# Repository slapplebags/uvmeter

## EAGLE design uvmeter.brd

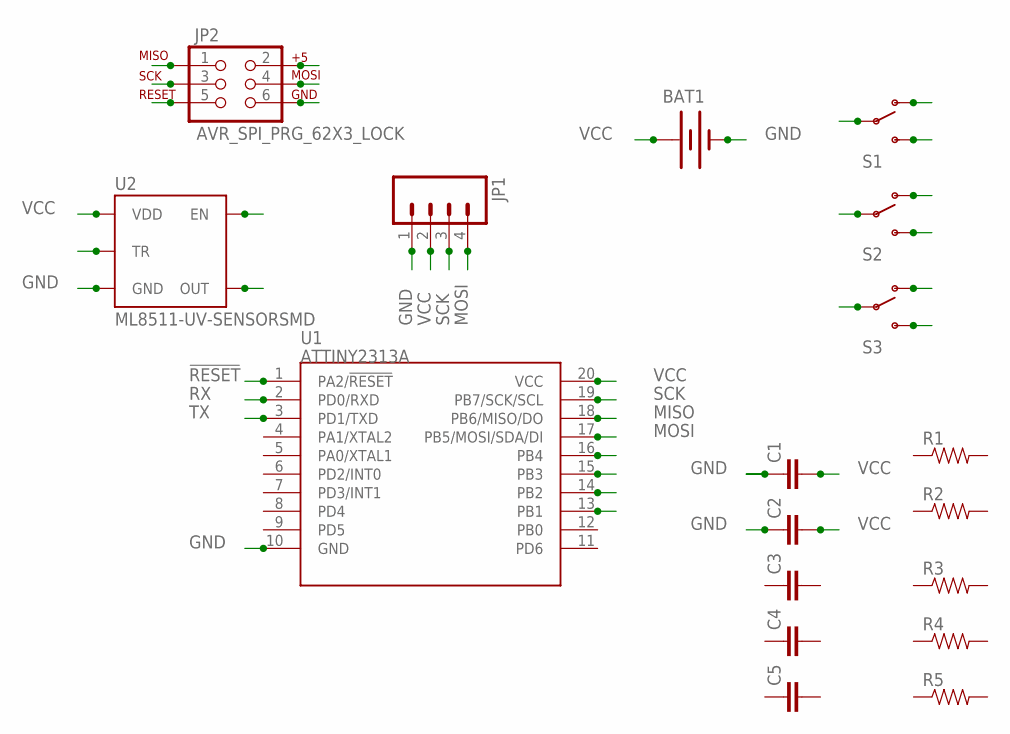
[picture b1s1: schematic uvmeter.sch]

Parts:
BAT1: BATTERY20SMD; BATTCON_20MM
C1, C2, C3, C4, C5: CAP0805; 0805
JP1: M04LONGPADS; 1X04_LONGPADS
JP2: AVR_SPI_PRG_62X3_LOCK; 2X3_LOCK
R1, R2, R3, R4, R5: RESISTOR0805-RES; 0805
S1, S2, S3: SWITCH-SPDTSMD2; SWITCH-SPDT-SMD
U1: ATTINY2313A; SOP20W
U2: ML8511-UV-SENSORSMD; ML8511

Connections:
!RESET: JP2.5, R2.1, U1.1 (PA2/!RESET)
D10: U1.13 (PB1)
D11: U1.14 (PB2)
D12: U1.15 (PB3)
D13: U1.16 (PB4)
EN: R1.1
GND: BAT1.2 (-), C1.1, C2.1, C3.1, JP1.1, JP2.6, U1.10 (GND), U2.5 (GND)
MISO: JP2.1, U1.18 (PB6/MISO/DO)
MOSI: JP1.4, JP2.4, R4.1, U1.17 (PB5/MOSI/SDA/DI)
RX: U1.2 (PD0/RXD)
SCK: JP1.3, JP2.3, R3.1, U1.19 (PB7/SCK/SCL)
TR: C3.2, U2.10 (TR)
TX: U1.3 (PD1/TXD)
VCC: BAT1.1 (+), C1.2, C2.2, JP1.2, JP2.2, R1.2, R2.2, R3.2, R4.2, U1.20 (VCC), U2.7 (VDD)

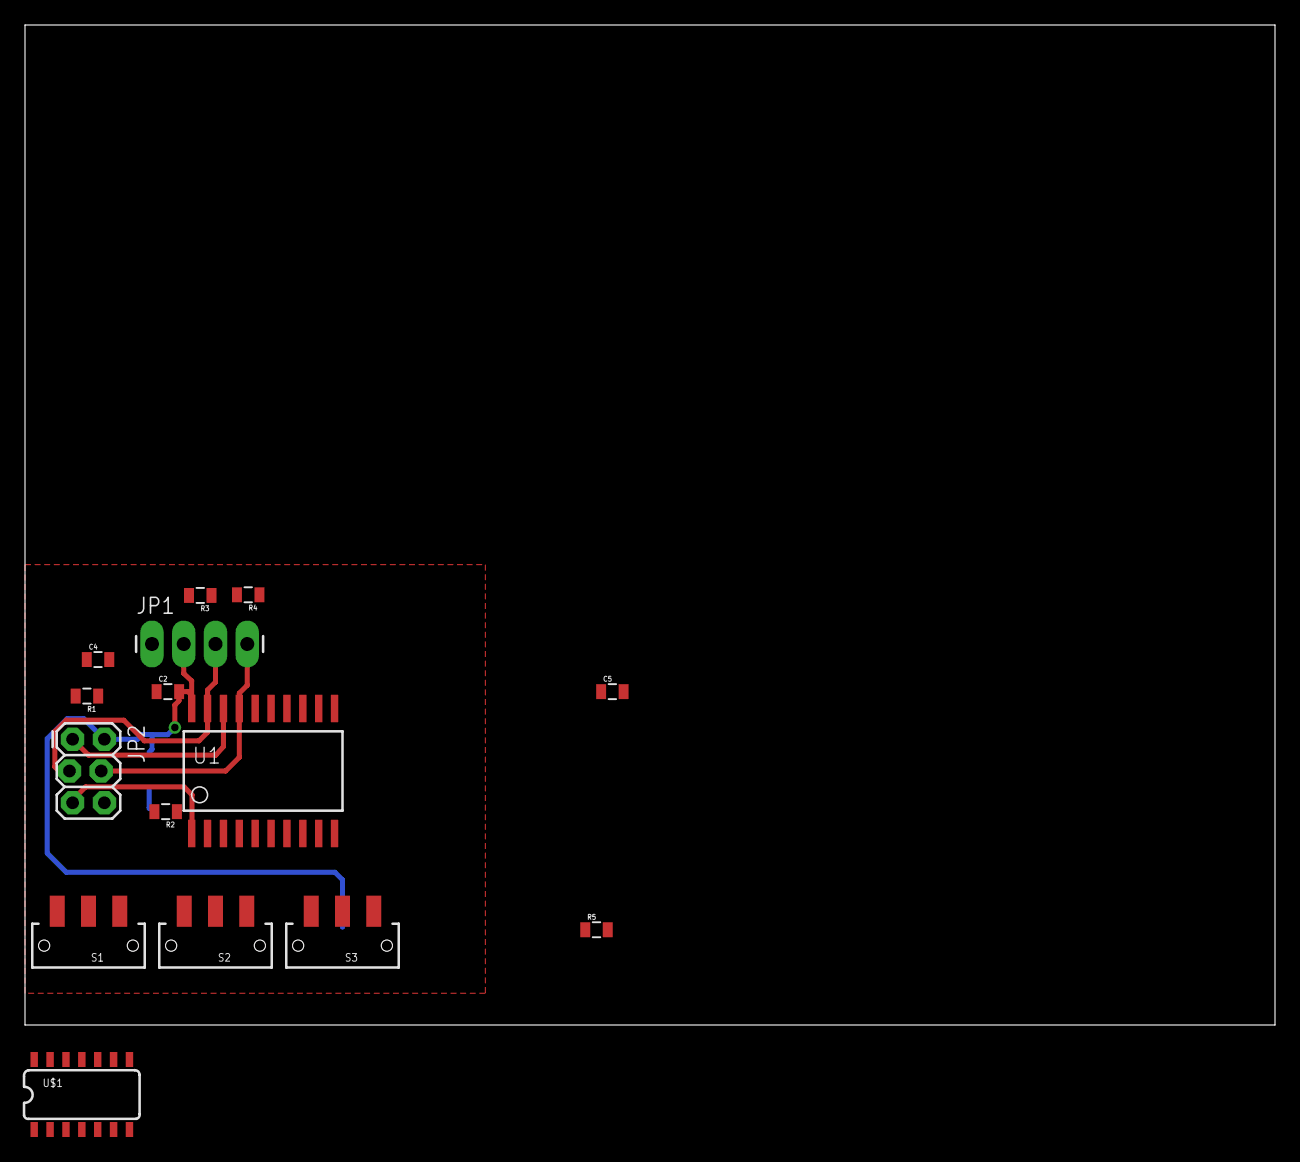
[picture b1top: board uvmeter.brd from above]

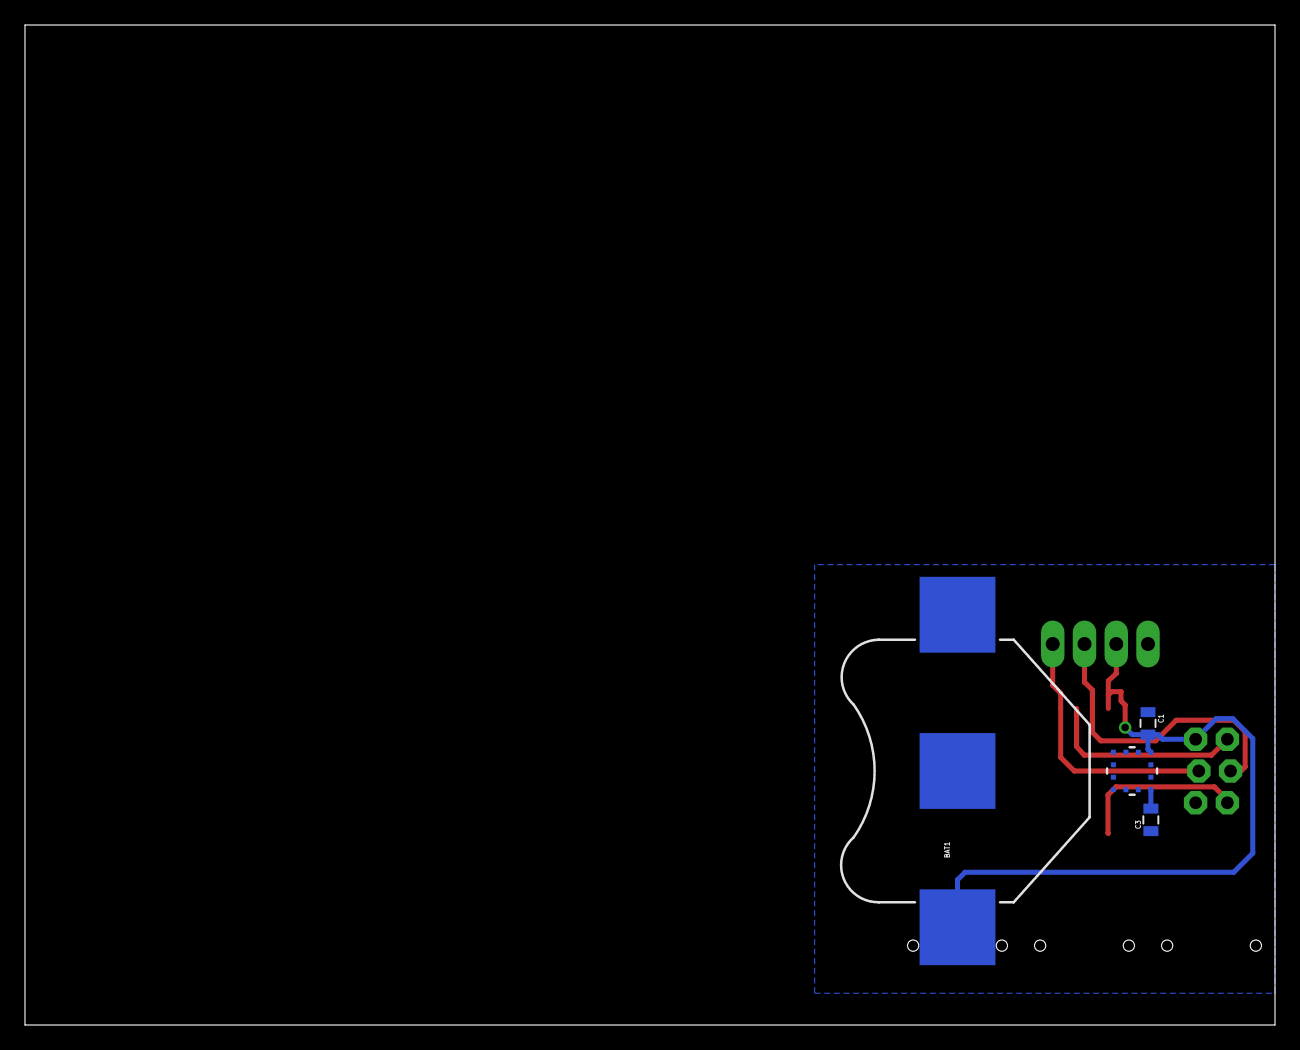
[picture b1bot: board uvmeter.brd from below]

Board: 2 copper layers, 100.0 x 80.0 mm, 19 parts (4 on the bottom side), 7 nets.

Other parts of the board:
U$1: ATTINY84; SO14

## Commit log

2015-12-04 all parts added
2015-12-04 connected decoupling caps
2015-12-04 added attiny84
    attiny2313 doesn’t have an onboard adc, swapping it out for an attyin84

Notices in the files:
parts and their libraries:
SparkFun-DigitalIC: Licensing: Creative Commons ShareAlike 4.0 International - https://creativecommons.org/licenses/by-sa/4.0
